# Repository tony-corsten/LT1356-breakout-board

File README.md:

# LT1356-breakout-board
# Overview
The LT1356 is a quad-input op-amp with high slew rate, fast settling time, low input noise and a wide supply voltage range, making it a fantastic ADC driver for ADCs with +/- 10V swings. It's a great choice for projects that want to conserve board space, but still need a lot of inputs. [You can find the official documentation for the chip here.](https://www.analog.com/en/products/lt1356.html). This is a breakout board made in Kicad with dedicated headers for a power supply input and for input voltages. 

*_Note_*: The board is currently designed as a buffer amplifier. Make sure to edit the design if you want non-unity gain. A future update of the design will include a schematic setup for a non-inverting amplifier on each input. 

# Navigating this repo
The main folder contains relevant Kicad files (.pro, .pcb, .sch). The `gerber` directory has a PCB-fabrication ready set of gerber files. The `library` directory has a custom footprint (.kicad_mod) that works for the SOP version of this chip. The official Analog part file for the chip (.lib) can also be found there.

# Board images
PCB Layout:

Schematic:

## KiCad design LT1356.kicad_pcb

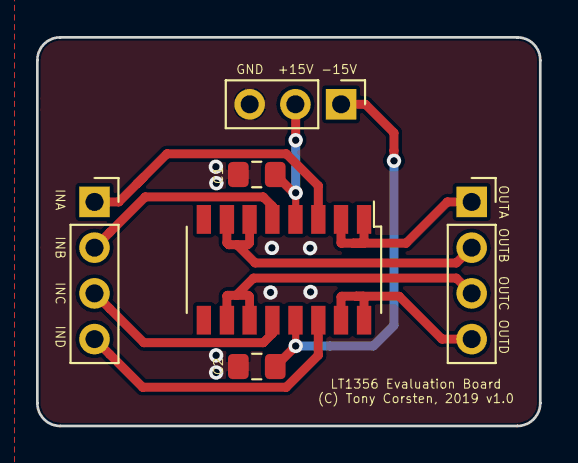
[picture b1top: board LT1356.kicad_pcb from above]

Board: 2 copper layers, 27.9 x 21.6 mm, 6 parts (0 on the bottom side), 11 nets.

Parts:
C1, C2: C_Small; C_0805_2012Metric_Pad1.15x1.40mm_HandSolder
J1: Conn_01x03_Male; PinHeader_1x03_P2.54mm_Vertical
J2: SIG_IN; PinSocket_1x04_P2.54mm_Vertical
J3: SIG_OUT; PinSocket_1x04_P2.54mm_Vertical
U1: LT1356IS-PBF; SOP-16_3.9x10.4mm_P1.27mm_Hand_Solder

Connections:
+15V: C1.1, J1.2, U1.4
-15V: C2.2, J1.1, U1.13
/INA: J2.1, U1.3
/INB: J2.2, U1.5
/INC: J2.3, U1.12
/IND: J2.4, U1.14
/OUTA: J3.1, U1.1, U1.2
/OUTB: J3.2, U1.6, U1.7
/OUTC: J3.3, U1.10, U1.11
/OUTD: J3.4, U1.15, U1.16
GND: C1.2, C2.1, J1.3

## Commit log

2019-08-17 intial commit
2019-08-17 added library for footprint and part
2019-08-17 explicitly listed capacitor values
